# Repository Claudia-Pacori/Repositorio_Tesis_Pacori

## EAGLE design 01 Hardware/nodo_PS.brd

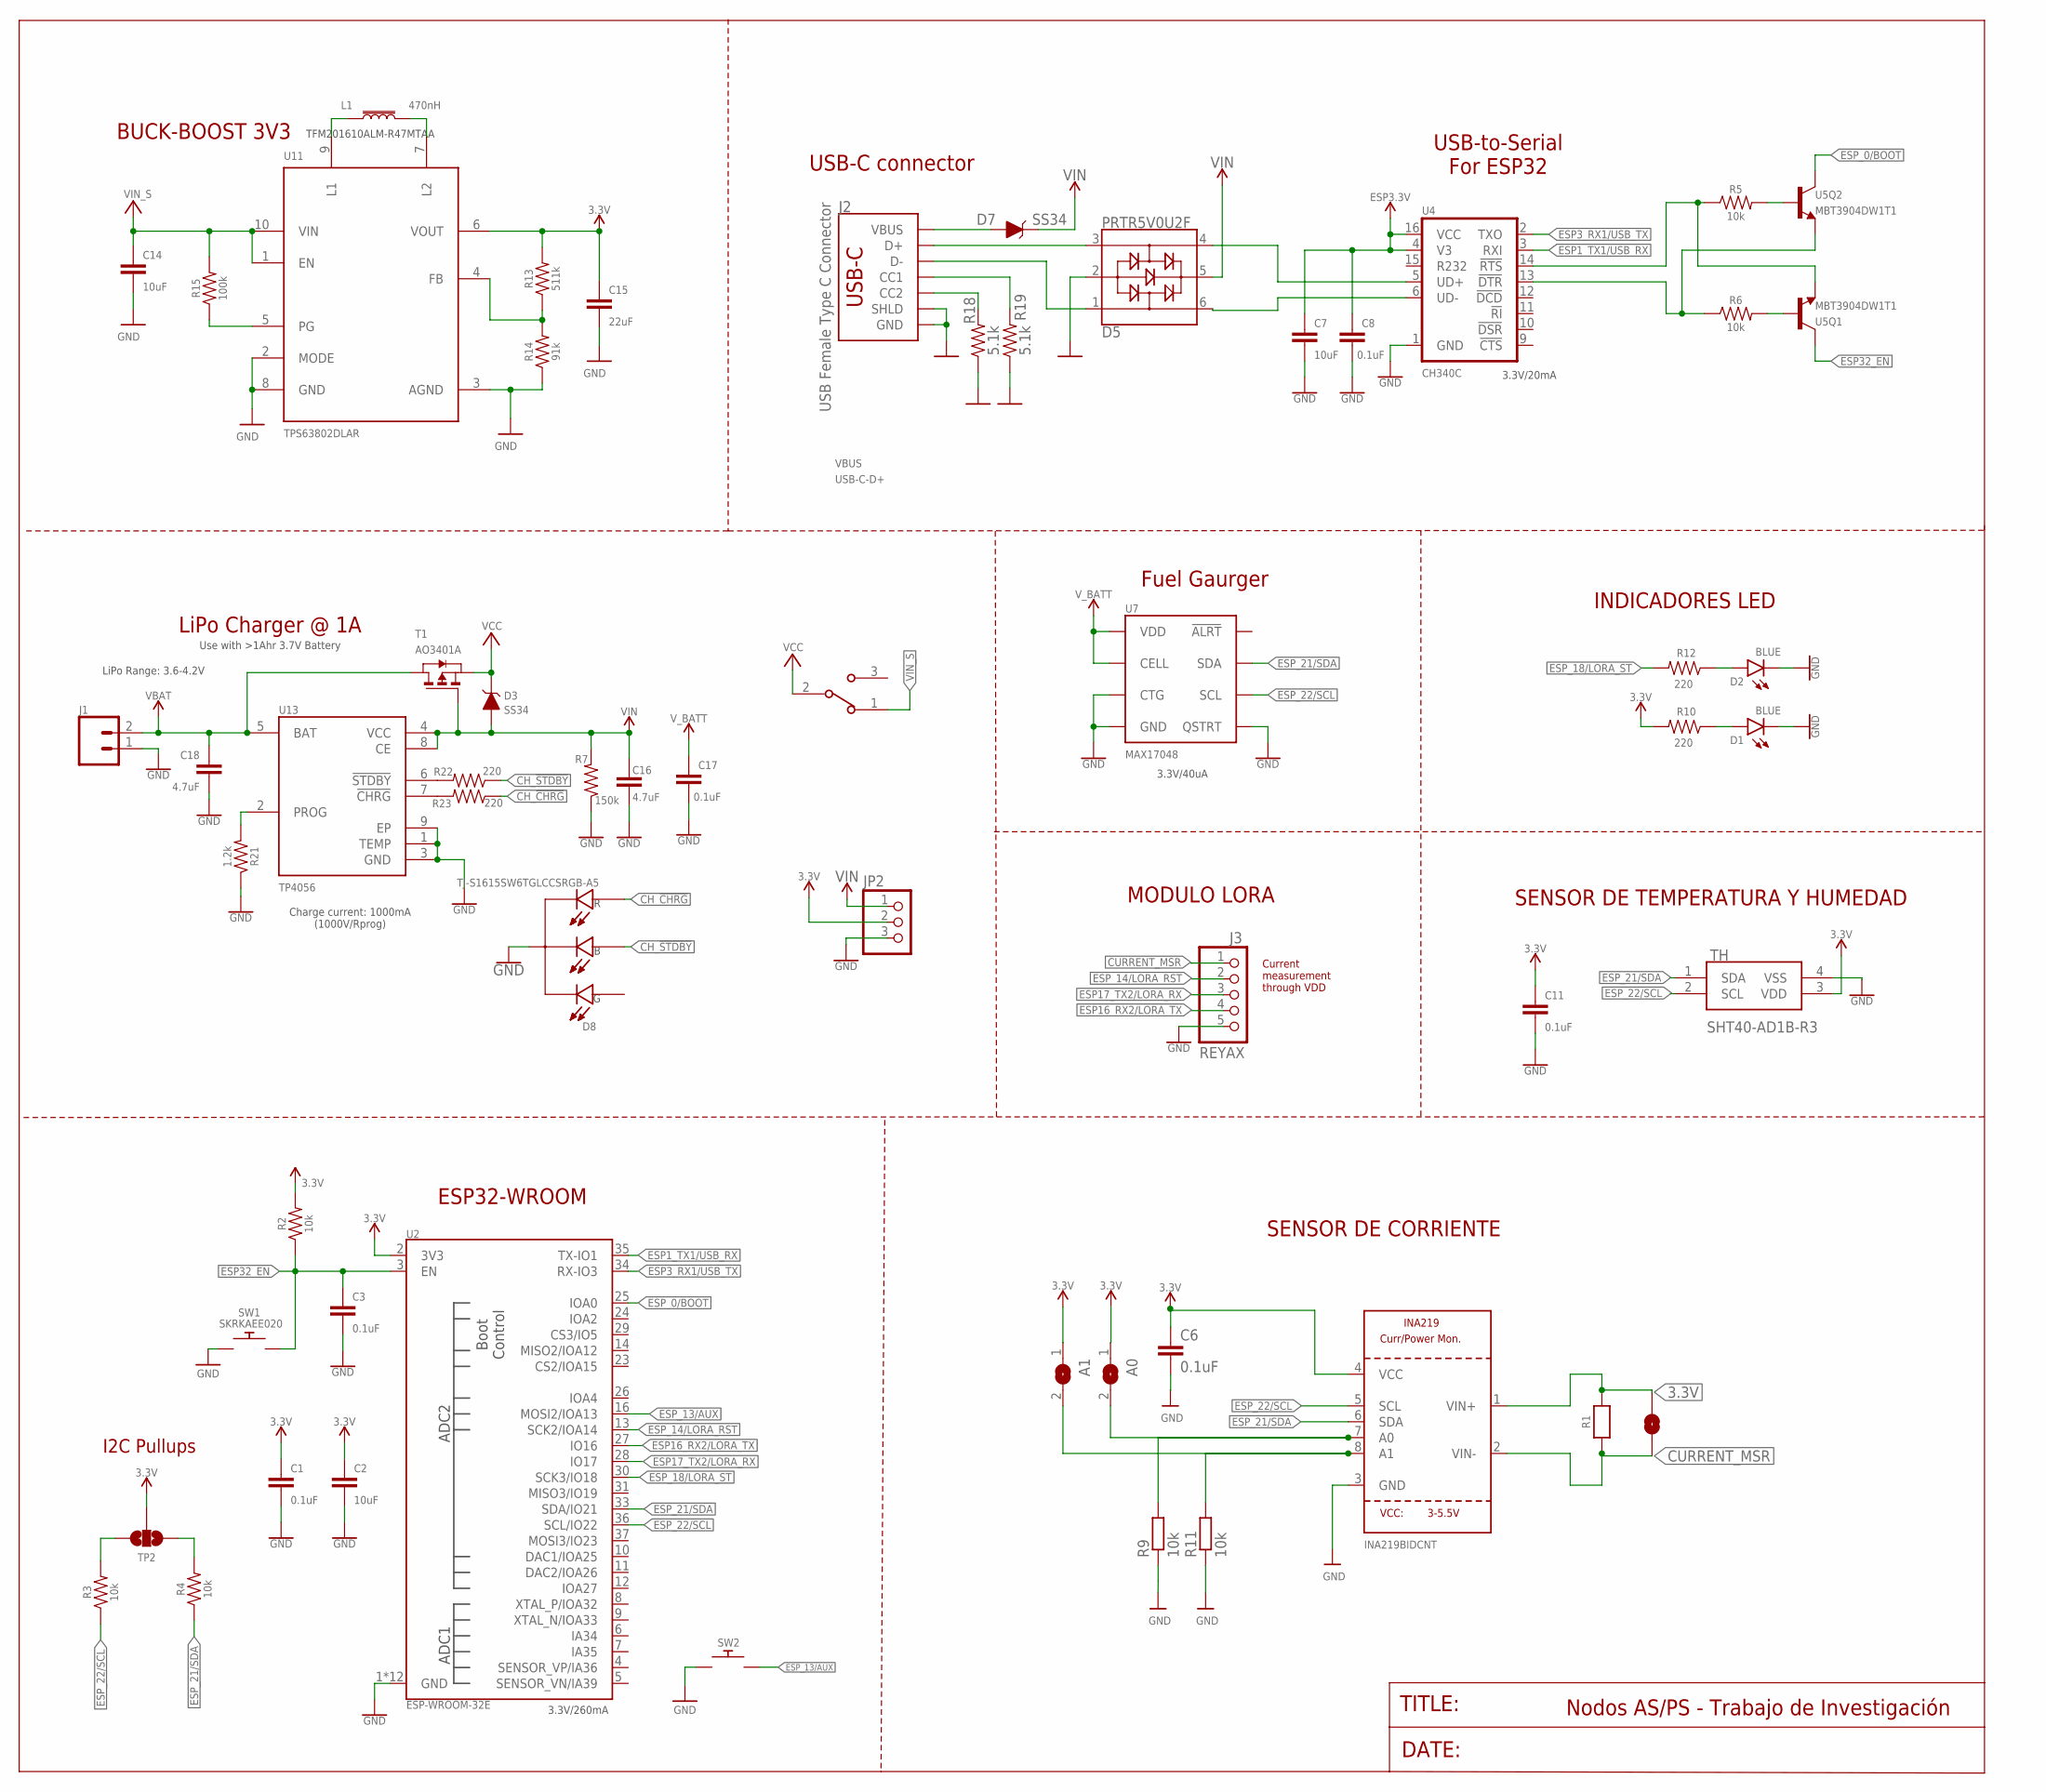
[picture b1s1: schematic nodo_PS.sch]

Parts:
A0, A1: SOLDERJUMPERREFLOW_NOPASTE; SOLDERJUMPER_REFLOW_NOPASTE
C1, C3, C8, C11, C17: 0.1uF; 0603
C2, C7: 10uF; 0603
C6: 0.1uF; C0805
C14: 10uF; 1206
C15: 22uF; 1206
C16, C18: 4.7uF; 0603
D1, D2: BLUE; LED-0603
D3, D7: SS34; DO-214AC
D5: PRTR5V0U2F; SOT886
D8: TJ-S1615SW6TGLCCSRGB-A5; LED_OSTB0603C1C
J1: CONN_02LOCK_LONGPADS; 1X02_LOCK_LONGPADS
J2: USB Female Type C Connector; USB-C-16P_4LAYER-PADS
J3: REYAX; 1X05
JP1: JUMPER-SMT_2_NO_NO-SILK_ROUND; SMT-JUMPER_2_NO_NO-SILK_ROUND
JP2: PINHD-1X3; 1X03
L1: 470nH; 0805
R1: 0.1/1% (PT2512FK-070R1L); 2512
R2, R3, R4, R5, R6: 10k; 0603
R7: 150k; 0603
R9, R11: 10k; R0805
R10, R12, R22, R23: 220; 0603
R13: 511k; 0603
R14: 91k; 0603
R15: 100k; 0603
R18, R19: 5.1k; 0603
R21: 1.2k; 0603
S1: EG1213; SW_EG1213
SENSORCORRIENTE: INA219BIDCNT; SOT23-8
SW1, SW2: SKRKAEE020
T1: AO3401A; SOT-23
TH: SHT40-AD1B-R3; SHT40AD1BR3
TP2: JUMPER-SMT_3_NO_NO-SILK; SMT-JUMPER_3_NO_NO-SILK
U2: ESP-WROOM-32E; ESP-WROOM-32D-NARROW
U4: CH340C; SO016
U5: MBT3904DW1T1; SC70-6
U7: MAX17048; DFN-8
U11: TPS63802DLAR; VREG_TPS63802DLAR
U13: TP4056; SOP127P600X175-9N

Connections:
3.3V: A0.1, A1.1, C1.1, C2.1, C6.1, C7.1, C8.1, C11.1, C15.1, JP1.1, JP2.2, R1.2, R2.2, R10.2, R13.2, SENSORCORRIENTE.1 (VIN+), SENSORCORRIENTE.4 (VCC), TH.3 (VDD), TP2.2, U2.2 (3V3), U4.4 (V3), U4.16 (VCC), U11.6 (VOUT)
ADDR0: A0.2, R9.2, SENSORCORRIENTE.7 (A0)
ADDR1: A1.2, R11.2, SENSORCORRIENTE.8 (A1)
CC1: J2.B5 (CC2), R18.2
CC2: J2.A5 (CC1), R19.2
CH_!CHRG: D8.3, R23.1
CH_!STDBY: D8.2, R22.1
CURRENT_MSR: J3.1, JP1.2, R1.1, SENSORCORRIENTE.2 (VIN-)
ESP1_TX1/USB_RX: U2.35 (TX-IO1), U4.3 (RXI)
ESP3_RX1/USB_TX: U2.34 (RX-IO3), U4.2 (TXO)
ESP16_RX2/LORA_TX: J3.4, U2.27 (IO16)
ESP17_TX2/LORA_RX: J3.3, U2.28 (IO17)
ESP32_!DTR: R6.1, U4.13 (!DTR), U5.1 (E)
ESP32_!RTS: R5.1, U4.14 (!RTS), U5.4 (E)
ESP32_EN: C3.1, R2.1, SW1.2, U2.3 (EN), U5.3 (C)
ESP_0/BOOT: U2.25 (IOA0), U5.6 (C)
ESP_13/AUX: SW2.2, U2.16 (MOSI2/IOA13)
ESP_14/LORA_RST: J3.2, U2.13 (SCK2/IOA14)
ESP_18/LORA_ST: R12.2, U2.30 (SCK3/IO18)
ESP_21/SDA: R4.1, SENSORCORRIENTE.6 (SDA), TH.1 (SDA), U2.33 (SDA/IO21), U7.8 (SDA)
ESP_22/SCL: R3.1, SENSORCORRIENTE.5 (SCL), TH.2 (SCL), U2.36 (SCL/IO22), U7.7 (SCL)
GND: C1.2, C2.2, C3.2, C6.2, C7.2, C8.2, C11.2, C14.2, C15.2, C16.2, C17.2, C18.2, D1.C, D2.C, D5.2, D8.4, J1.1, J2.GND, J2.GND2 (GND), J2.SHLD2 (SHLD), J2.SHLD3 (SHLD), J2.SHLD4 (SHLD), J2.SHLD5 (SHLD), J3.5, JP2.3, R7.1, R9.1, R11.1, R14.1, R18.1, R19.1, R21.1, SENSORCORRIENTE.3 (GND), SW1.1, SW2.1, TH.4 (VSS), U2.1 (GND), U2.15 (GND), U2.38 (GND), U2.GND1 (GND), U2.GNDT1 (GND), U2.GNDT2 (GND), U2.GNDT3 (GND), U2.GNDT4 (GND), U2.GNDT5 (GND), U2.GNDT6 (GND), U2.GNDT7 (GND), U2.GNDT8 (GND), U4.1 (GND), U7.1 (CTG), U7.4 (GND), U7.6 (QSTRT), U7.9 (GND), U11.2 (MODE), U11.3 (AGND), U11.8 (GND), U13.1 (TEMP), U13.3 (GND), U13.9 (EP)
unnamed: D5.1, J2.A7 (D-), J2.B7 (D-)
unnamed: D5.4, U4.5 (UD+)
unnamed: D5.6, U4.6 (UD-)
unnamed: D1.A, R10.1
unnamed: D2.A, R12.1
unnamed: L1.1, U11.9 (L1)
unnamed: L1.2, U11.7 (L2)
unnamed: R22.2, U13.6 (!STDBY)
unnamed: R13.1, R14.2, U11.4 (FB)
unnamed: R23.2, U13.7 (!CHRG)
unnamed: R3.2, TP2.3
unnamed: R4.2, TP2.1
unnamed: R15.1, U11.5 (PG)
unnamed: R6.2, U5.5 (B)
unnamed: R5.2, U5.2 (B)
unnamed: R21.2, U13.2 (PROG)
USB-C-D+: D5.3, J2.A6 (D+), J2.B6 (D+)
VBAT: C17.1, C18.1, J1.2, T1.1 (D), U7.2 (CELL), U7.3 (VDD), U13.5 (BAT)
VBUS: D7.A, J2.VBUS1 (VBUS), J2.VBUS2 (VBUS)
VCC: D3.C, S1.2, T1.2 (S)
VIN: C16.1, D3.A, D5.5, D7.C, JP2.1, R7.2, T1.3 (G), U13.4 (VCC), U13.8 (CE)
VIN_S: C14.1, R15.2, S1.1, U11.1 (EN), U11.10 (VIN)

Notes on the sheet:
ESP32-WROOM
3.3V/260mA
SENSOR DE TEMPERATURA Y HUMEDAD
SENSOR DE CORRIENTE
USB-to-Serial For ESP32
3.3V/20mA
USB-C connector
LiPo Range: 3.6-4.2V
Charge current: 1000mA (1000V/Rprog)
Use with >1Ahr 3.7V Battery
LiPo Charger @ 1A
Fuel Gaurger
3.3V/40uA
Nodos AS/PS - Trabajo de Investigación
TITLE:
DATE:
BUCK-BOOST 3V3
TFM201610ALM-R47MTAA
INDICADORES LED
I2C Pullups
MODULO LORA
Current measurement through VDD

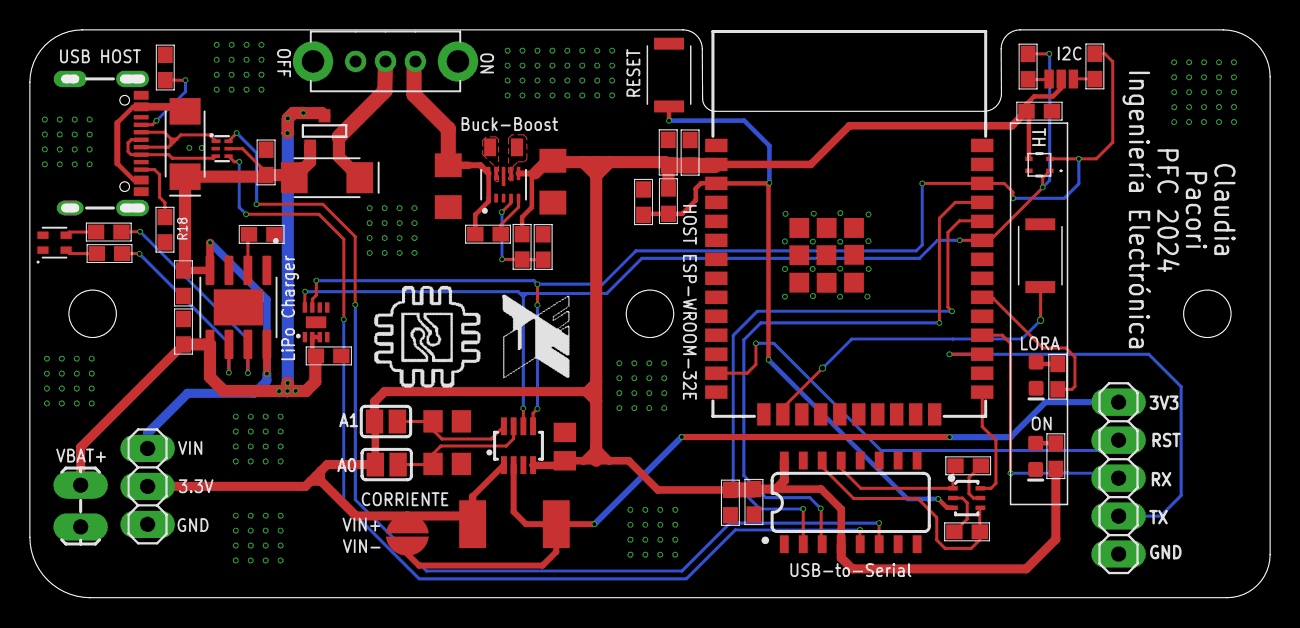
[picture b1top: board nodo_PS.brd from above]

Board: 2 copper layers, 82.4 x 37.4 mm, 58 parts (0 on the bottom side), 44 nets.

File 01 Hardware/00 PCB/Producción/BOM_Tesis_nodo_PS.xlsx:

Comment | Part | Footprint | Value | Designator
CC0603KRX7R9BB104 | C14663 | C0603 | 0.1uF | C1
CL10A106KP8NNNC | C19702 | C0603 | 10uF | C2
CC0603KRX7R9BB104 | C14663 | C0603 | 0.1uF | C3
CC0805KRX7R9BB104 | C49678 | C0805 | 0.1uF | C6
CL10A106KP8NNNC | C19702 | C0603 | 10uF | C7
CC0603KRX7R9BB104 | C14663 | C0603 | 0.1uF | C8
CC0603KRX7R9BB104 | C14663 | C0603 | 0.1uF | C11
CL31A106KBHNNNE | C13585 | C1206 | 10uF | C14
CL31A226KPHNNNE | C5672 | C1206 | 22uF | C15
CL10A475KO8NNNC | C19666 | C0603 | 4.7uF | C16
CC0603KRX7R9BB104 | C14663 | C0603 | 0.1uF | C17
CL10A475KO8NNNC | C19666 | C0603 | 4.7uF | C18
YLED0603B | C19171394 | LED-0603 | BLUE | D1
YLED0603B | C19171394 | LED-0603 | BLUE | D2
SS34 | C8678 | DO-214AC | SS34 | D3
PRTR5V0U2F,115 | C478118 | SOT886 | PRTR5V0U2F | D5
SS34 | C8678 | DO-214AC | SS34 | D7
TJ-S1615SW6TGLCCSRGB-A5 | C273611 | LED-0606 | TJ-S1615SW6TGLCCSRGB-A5 | D8
918-418K2023S40001 | C167321 | TYPE-C-SMD | USB-C FemaleConnector | J2
TFM201610ALM-R47MTAA | C501954 | 806 | 470nH | L1
25121WJ010KT4E | C419755 | R2512 | 0.1 | R1
0603WAF1002T5E | C25804 | R0603 | 10k | R2
0603WAF1002T5E | C25804 | R0603 | 10k | R3
0603WAF1002T5E | C25804 | R0603 | 10k | R4
0603WAF1002T5E | C25804 | R0603 | 10k | R5
0603WAF1002T5E | C25804 | R0603 | 10k | R6
0603WAF1503T5E | C22807 | R0603 | 150k | R7
0805W8F1002T5E | C17414 | R0805 | 10k | R9
0603WAF2200T5E | C22962 | R0603 | 220 | R10
0805W8F1002T5E | C17414 | R0805 | 10k | R11
0603WAF2200T5E | C22962 | R0603 | 220 | R12
0603WAF5113T5E | C23194 | R0603 | 511k | R13
0603WAJ0913T5E | C25610 | R0603 | 91k | R14
0603WAF1003T5E | C25803 | R0603 | 100k | R15
0603WAF5101T5E | C23186 | R0603 | 5.1k | R18
0603WAF5101T5E | C23186 | R0603 | 5.1k | R19
0603WAF1201T5E | C22765 | R0603 | 1.2k | R21
0603WAF2200T5E | C22962 | R0603 | 220 | R22
0603WAF2200T5E | C22962 | R0603 | 220 | R23
INA219BIDCNT | C2653868 | SOT23-8 | INA219BIDCNT | SENSORCORRIENTE
SKRKAEE020 | C115357 | SW-SMD-2_2.9x3.9x1.7 | SKRKAEE020 | SW1
SKRKAEE020 | C115357 | SW-SMD-2_2.9x3.9x1.7 | SKRKAEE020 | SW2
AO3401A | C15127 | SOT-23 | AO3401A | T1
SHT40-BD1B-R2 | C7461849 | SHT40BD1BR2 | SHT40-BD1B-R2 | TH
ESP32-WROOM-32E(16MB) | C701343 | ESP-WROOM-32D-NARROW | ESP-WROOM-32E | U2
CH340C | C84681 | SOP-16 | CH340C | U4
LMBT3904DW1T1G | C131781 | SOT-363 | MBT3904DW1T1 | U5
MAX17048G+T10 | C2682616 | TDFN-8_EP | MAX17048 | U7
TPS63802DLAR | C2845237 | VSON-10(2x3) | TPS63802DLAR | U11
TP4056-42-ESOP8 | C16581 | ESOP-8 | TP4056 | U13

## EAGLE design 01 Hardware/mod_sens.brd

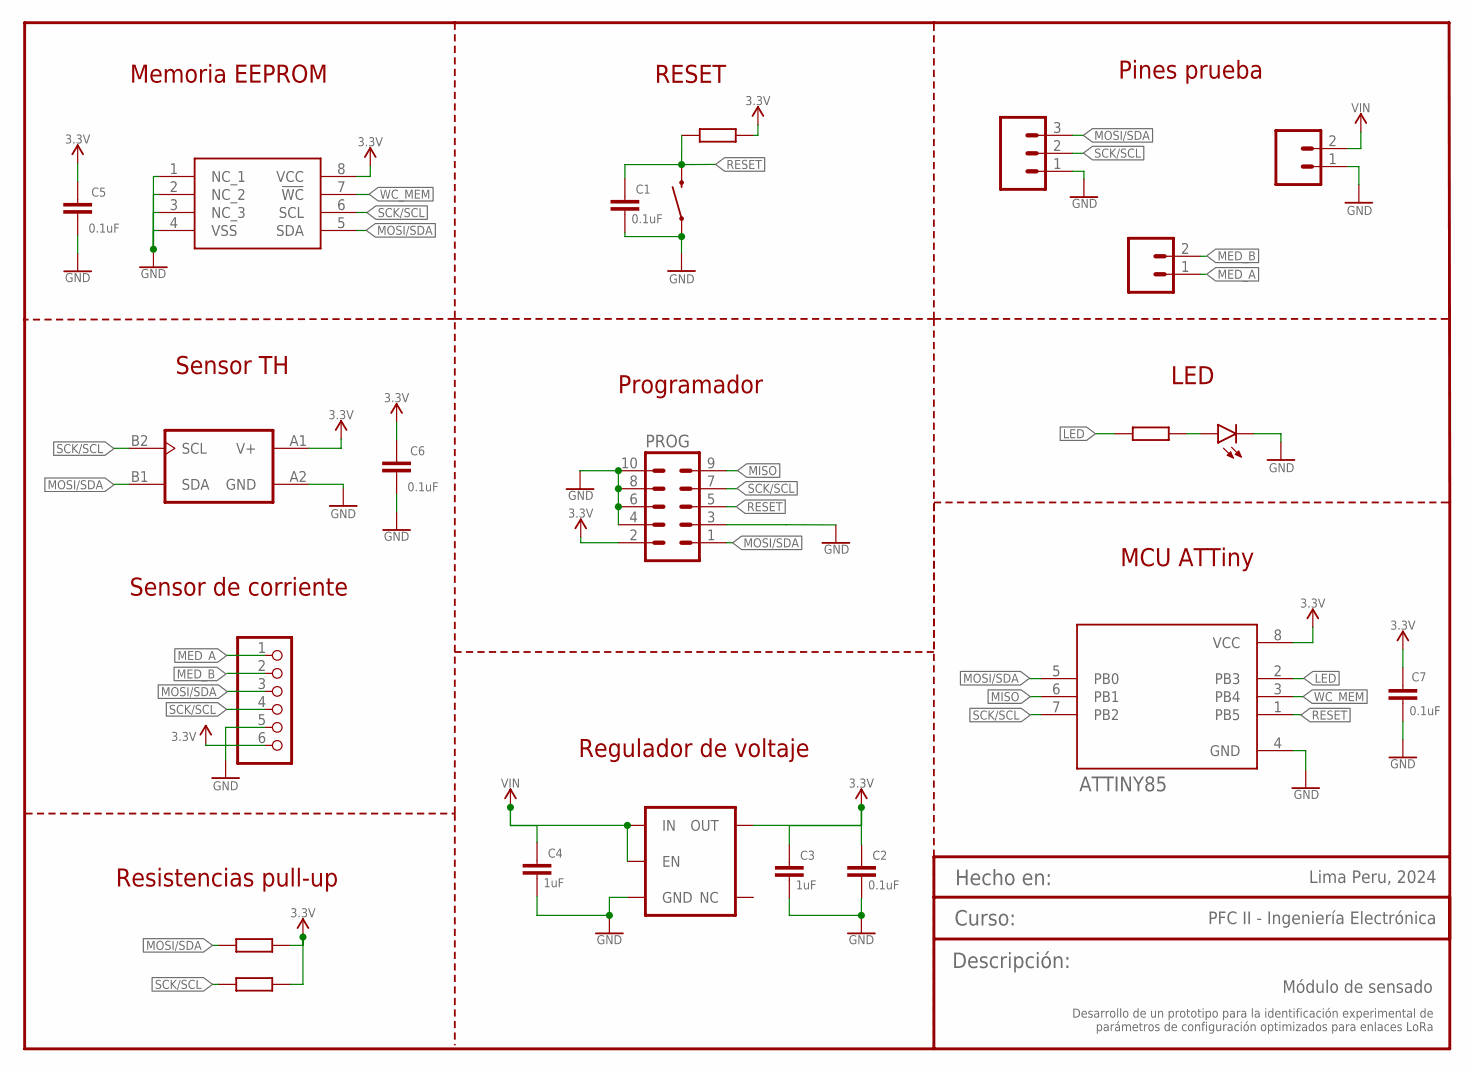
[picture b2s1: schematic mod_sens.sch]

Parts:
ATTINY85: ATTINY85; SOIC127P798X216-8N
C1, C2: 0.1uF; C0603K
C3, C4: 1uF; C0603K
C5, C6, C7: 0.1uF; 0603
CURR, CURR1: curr; 1X02
I2C: i2c; 1X03
L_ON: LED_3MM; LEDRD254W50D405H1055
MEMORIA: M24M01E; SOIC127P600X175-8N
PROG: ML10-3M; 3M_10
R1: 68; 0207/10
R2, R3: 1.5k; 0207/10
R4: 10k; 0207/10
RESET: MOMENTARY-SWITCH-SPST-PTH-6.0MM; TACTILE_SWITCH_PTH_6.0MM
SENSOR_CURR: sens_curr; 1X06
SENSOR_TH: TMP103GYFFR; IC_TMP103DYFFR
VOLT: 3.3V; SOT23-5

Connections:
3.3V: ATTINY85.8 (VCC), C2.1, C3.1, C5.1, C6.1, C7.1, MEMORIA.8 (VCC), PROG.2, R2.2, R3.2, R4.2, SENSOR_CURR.6, SENSOR_TH.A1 (V+), VOLT.5 (OUT)
GND: ATTINY85.4 (GND), C1.2, C2.2, C3.2, C4.2, C5.2, C6.2, C7.2, CURR1.1, I2C.1, L_ON.C, MEMORIA.1 (NC_1), MEMORIA.2 (NC_2), MEMORIA.3 (NC_3), MEMORIA.4 (VSS), PROG.3, PROG.4, PROG.6, PROG.8, PROG.10, RESET.1, SENSOR_CURR.5, SENSOR_TH.A2 (GND), VOLT.2 (GND)
LED: ATTINY85.2 (PB3), R1.1
MED_A: CURR.1, SENSOR_CURR.1
MED_B: CURR.2, SENSOR_CURR.2
MISO: ATTINY85.6 (PB1), PROG.9
MOSI/SDA: ATTINY85.5 (PB0), I2C.3, MEMORIA.5 (SDA), PROG.1, R2.1, SENSOR_CURR.3, SENSOR_TH.B1 (SDA)
unnamed: L_ON.A, R1.2
RESET: ATTINY85.1 (PB5), C1.1, PROG.5, R4.1, RESET.3 (2)
SCK/SCL: ATTINY85.7 (PB2), I2C.2, MEMORIA.6 (SCL), PROG.7, R3.1, SENSOR_CURR.4, SENSOR_TH.B2 (SCL)
VIN: C4.1, CURR1.2, VOLT.1 (IN), VOLT.3 (EN)
WC_MEM: ATTINY85.3 (PB4), MEMORIA.7 (!WC)

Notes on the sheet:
Regulador de voltaje
RESET
LED
Programador
MCU ATTiny
Memoria EEPROM
Sensor de corriente
Sensor TH
Pines prueba
Resistencias pull-up
PFC II - Ingeniería Electrónica
Hecho en:
Curso:
Descripción:
Lima Peru, 2024
Desarrollo de un prototipo para la identificación experimental de parámetros de configuración optimizados para enlaces LoRa
Módulo de sensado

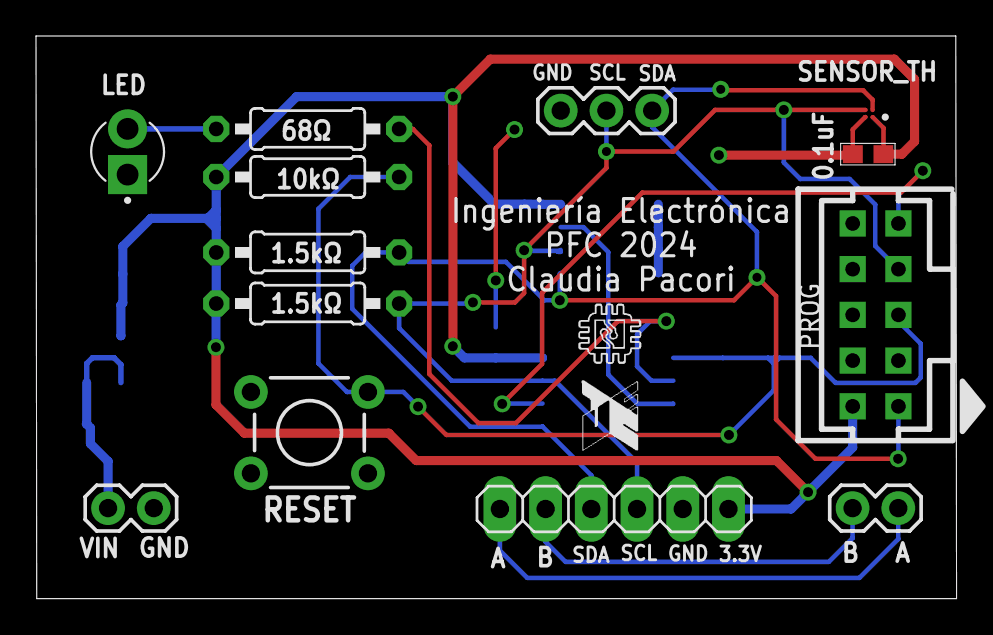
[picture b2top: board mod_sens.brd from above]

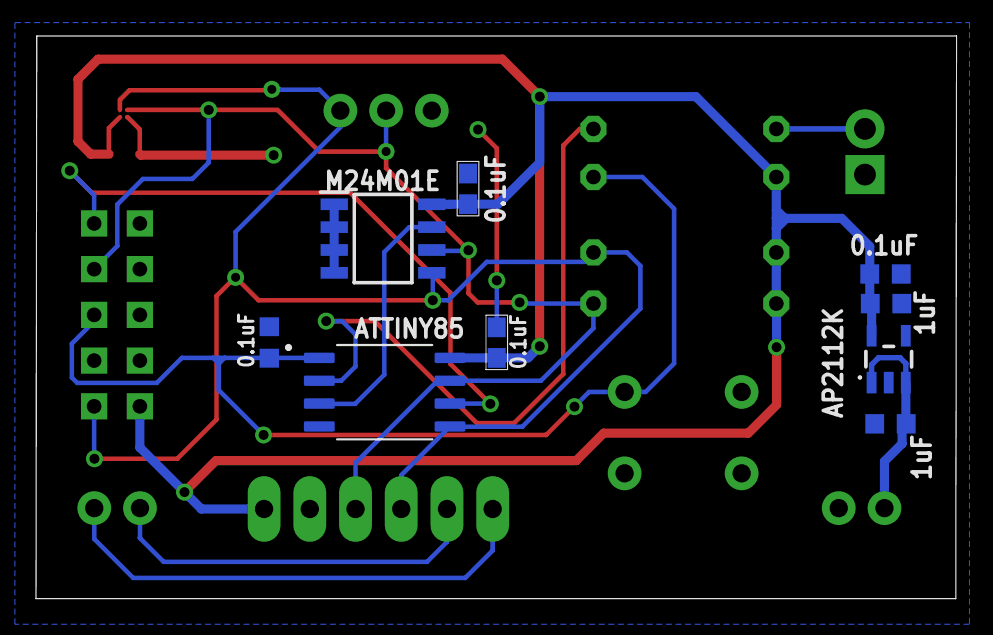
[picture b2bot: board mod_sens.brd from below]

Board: 2 copper layers, 51.1 x 31.3 mm, 22 parts (9 on the bottom side), 12 nets.

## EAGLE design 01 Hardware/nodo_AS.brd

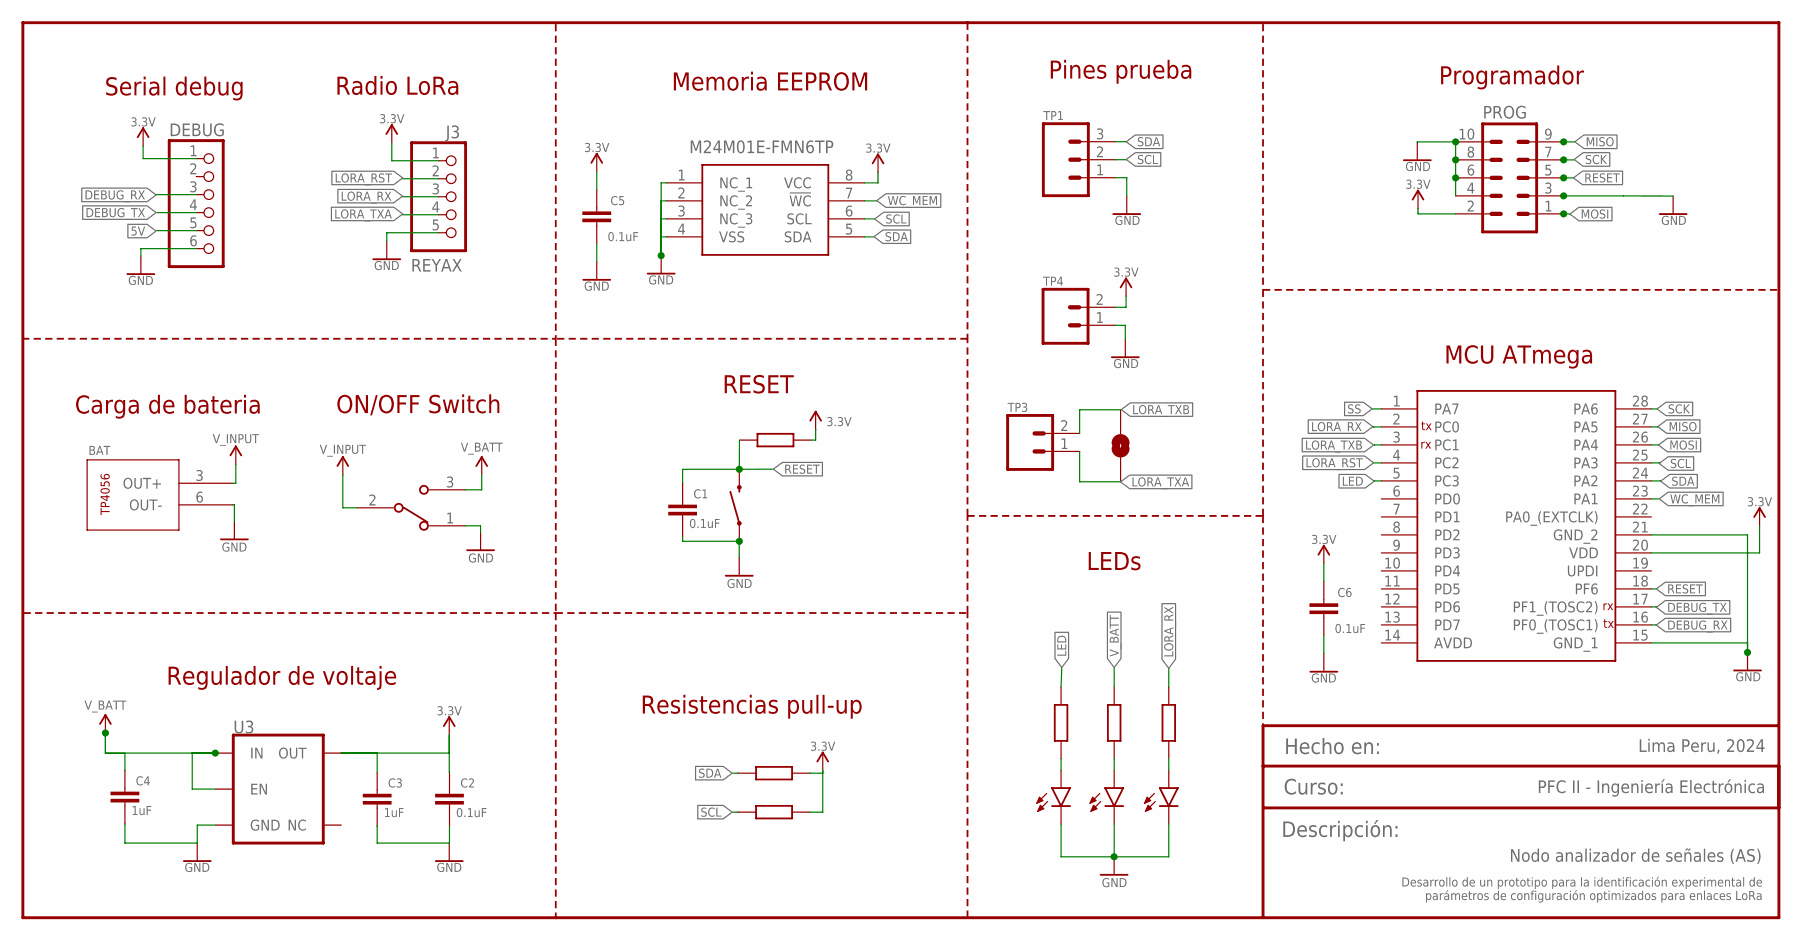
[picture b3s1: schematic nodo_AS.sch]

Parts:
BAT: TP4056MODULE
C1, C2: 0.1uF; C0603K
C3, C4: 1uF; C0603K
C5, C6: 0.1uF; 0603
DEBUG: PINHD-1X6; 1X06
IC1: ATMEGA3208-XU; SOP65P780X200-28N
IC2: M24M01E-FMN6TP; SOIC127P600X175-8N
J3: REYAX; 1X05
JP1: JUMPER-SMT_2_NO_NO-SILK_ROUND; SMT-JUMPER_2_NO_NO-SILK_ROUND
L_ON, L_ON1, L_ON2: LED_3MM; LEDRD254W50D405H1055
PROG: ML10-3M; 3M_10
P_RESET: MOMENTARY-SWITCH-SPST-PTH-6.0MM; TACTILE_SWITCH_PTH_6.0MM
R1, R2, R3: 68; 0207/10
R4: 10k; 0207/10
R6, R7: 1k; 0207/10
SW1: EG1213; SW_EG1213
TP1: CONN_03; 1X03
TP3, TP4: CONN_02; 1X02
U3: 3.3V; SOT23-5

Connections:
3.3V: C2.1, C3.1, C5.1, C6.1, DEBUG.1, IC1.20 (VDD), IC2.8 (VCC), J3.1, PROG.2, R4.2, R6.2, R7.2, TP4.2, U3.5 (OUT)
5V: DEBUG.5
DEBUG_RX: DEBUG.3, IC1.16 (PF0_(TOSC1))
DEBUG_TX: DEBUG.4, IC1.17 (PF1_(TOSC2))
GND: BAT.6 (OUT-), C1.2, C2.2, C3.2, C4.2, C5.2, C6.2, DEBUG.6, IC1.15 (GND_1), IC1.21 (GND_2), IC2.1 (NC_1), IC2.2 (NC_2), IC2.3 (NC_3), IC2.4 (VSS), J3.5, L_ON.C, L_ON1.C, L_ON2.C, PROG.3, PROG.4, PROG.6, PROG.8, PROG.10, P_RESET.1, SW1.1, TP1.1, TP4.1, U3.2 (GND)
LED: IC1.5 (PC3), R3.1
LORA_RST: IC1.4 (PC2), J3.2
LORA_RX: IC1.2 (PC0), J3.3, R1.1
LORA_TXA: J3.4, JP1.2, TP3.1
LORA_TXB: IC1.3 (PC1), JP1.1, TP3.2
MISO: IC1.27 (PA5), PROG.9
MOSI: IC1.26 (PA4), PROG.1
unnamed: L_ON.A, R3.2
unnamed: L_ON1.A, R2.2
unnamed: L_ON2.A, R1.2
RESET: C1.1, IC1.18 (PF6), PROG.5, P_RESET.3 (2), R4.1
SCK: IC1.28 (PA6), PROG.7
SCL: IC1.25 (PA3), IC2.6 (SCL), R7.1, TP1.2
SDA: IC1.24 (PA2), IC2.5 (SDA), R6.1, TP1.3
SS: IC1.1 (PA7)
V_BATT: C4.1, R2.1, SW1.3, U3.1 (IN), U3.3 (EN)
V_INPUT: BAT.3 (OUT+), SW1.2
WC_MEM: IC1.23 (PA1), IC2.7 (!WC)

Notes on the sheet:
Radio LoRa
LEDs
MCU ATmega
Programador
RESET
Regulador de voltaje
Pines prueba
Memoria EEPROM
Serial debug
ON/OFF Switch
Carga de bateria
Resistencias pull-up
PFC II - Ingeniería Electrónica
Hecho en:
Curso:
Descripción:
Lima Peru, 2024
Desarrollo de un prototipo para la identificación experimental de parámetros de configuración optimizados para enlaces LoRa
Nodo analizador de señales (AS)

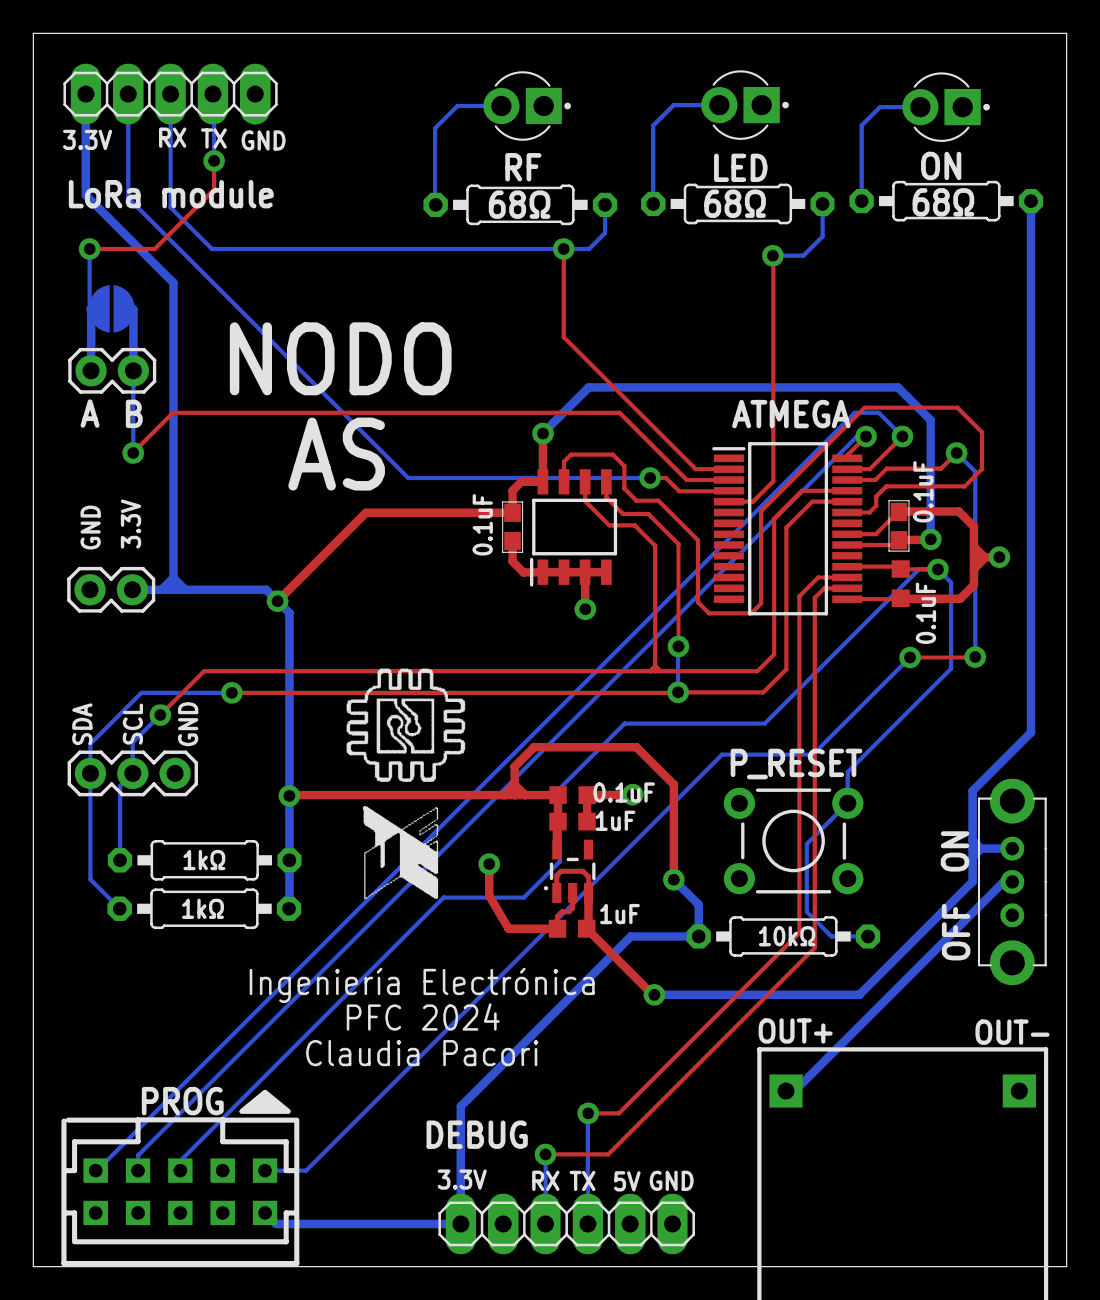
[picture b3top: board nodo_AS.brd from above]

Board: 2 copper layers, 62.0 x 74.0 mm, 28 parts (1 on the bottom side), 21 nets.

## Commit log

2024-05-31 hardware files
2024-09-16 actualizacion de archivos 24-2
2024-09-16 frmw files clear
2024-09-16 new readme
2024-10-21 actualización de archivos. HW final, FW v1
2024-12-03 update firmware
2024-12-04 pruebas code

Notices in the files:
parts and their libraries:
SparkFun-Switches: Licensing: Creative Commons ShareAlike 4.0 International - https://creativecommons.org/licenses/by-sa/4.0
